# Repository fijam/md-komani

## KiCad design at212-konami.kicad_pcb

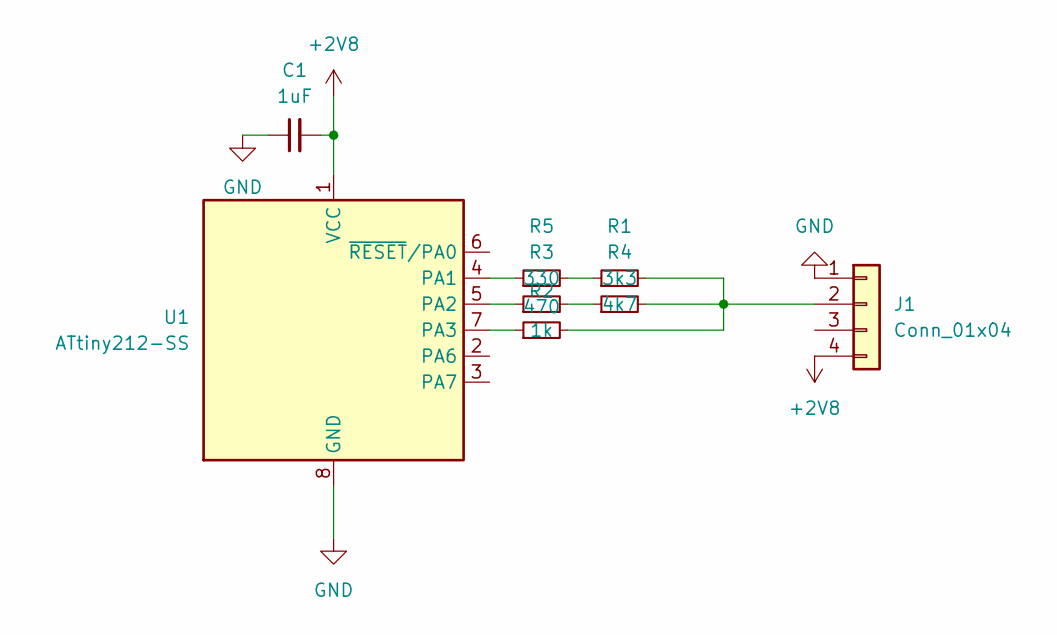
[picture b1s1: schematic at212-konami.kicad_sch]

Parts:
C1: 1uF; C_0805_2012Metric_Pad1.18x1.45mm_HandSolder
J1: Conn_01x04; Connector_Sony_Remote
R1: 3k3; R_0805_2012Metric
R2: 1k; R_0805_2012Metric_Pad1.20x1.40mm_HandSolder
R3: 470; R_0805_2012Metric
R4: 4k7; R_0805_2012Metric
R5: 330; R_0805_2012Metric
U1: ATtiny212-SS; SOIC-8_3.9x4.9mm_P1.27mm

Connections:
+2V8: C1.2, J1.4, U1.1 (VCC)
GND: C1.1, J1.1, U1.8 (GND)
unnamed: J1.2, R1.2, R2.2, R4.2
unnamed: R1.1, R5.2
unnamed: R3.2, R4.1
unnamed: R5.1, U1.4 (PA1)
unnamed: R3.1, U1.5 (PA2)
unnamed: R2.1, U1.7 (PA3)

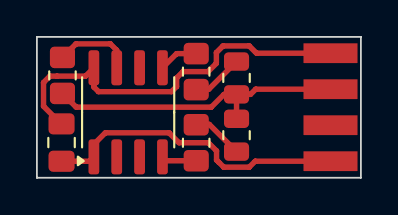
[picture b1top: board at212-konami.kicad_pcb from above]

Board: 2 copper layers, 18.0 x 7.8 mm, 8 parts (0 on the bottom side), 8 nets.
